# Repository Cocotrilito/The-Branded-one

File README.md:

<div align="center">

# The Branded One

*A tribute to Kentaro Miura's legacy.*

<br>

</div>

---

## Overview

A Berserk-themed NFC business card.
No battery.
No switches.
Powered entirely by your phone's NFC field.
Tap it and it opens my GitHub.

Built as a tribute to Guts' philosophy: **keep moving forward, no matter what.**

---

## The Tap

<p align="center">
  <i>No battery. No switches. Just the phone's field.</i>
</p>

---

## In Real Life

<p align="center">
  <i>The Branded One carried as it was meant to be.</i>
</p>

<br>

---

## The reason behind this project

> This project started with the Idea of showing a little bit of respect or give some honor for one of the most influencial characters in my adolescence, Gats or Guts or Gustavo in spanish, I wanted to do the business card, but It did not felt like me what can I say... I did not liked the Idea of a plain card, and is not useful Imo, so instead of a business card, why not a meaningfull memento, you see Guts really inspired me to keep going, probably thanks to what I read when I was younger I am who I am now, theres this quote of Guts that really hits me, it says...
>
> **I'm not going to die here.**
>
> to me it represents my hunger for not dying as a normal human being, everyday I try to do something to push me more, and its because I dont wanna be normal, and I started having sparks of this type of life, when Guts went out on a journey, leaving to become someone, thats when I thought,
>
> **Why am I not doing that...**
>
> thanks Guts, probably I will never see the ending of Berserk, but it did teach me to not give up, even when you dont think is worth it to try one more time, when you are worried about what will happen, you have to think the real reason you started, and in the process dont try to always be happy, just live because life is about living the present, not the past neither the future.
>
> **If Guts did not surrender, Why would you?**

---

## Schematic

---

## PCB

<table>
  <tr>
    <td width="50%"></td>
    <td width="50%"></td>
  </tr>
  <tr>
    <td align="center"><b>Front Copper</b></td>
    <td align="center"><b>Back Copper</b></td>
  </tr>
</table>

---

## Renders

<table>
  <tr>
    <td width="50%"></td>
    <td width="50%"></td>
  </tr>
  <tr>
    <td align="center"><b>Front</b></td>
    <td align="center"><b>Back</b></td>
  </tr>
</table>

---

## Bill of Materials

| Name | Purpose | Qty | Total Cost (USD) | Link |
| :--- | :--- | :---: | :---: | :--- |
| NT3H2111W0FHKH | NFC Controller | 1 | 0.62 | [LCSC](https://www.lcsc.com/product-detail/C710403.html) |
| Red LED 0603 | Status LED | 1 | 0.02 | [LCSC](https://www.lcsc.com/product-detail/C2286.html) |
| 1kΩ Resistor | LED Protection | 1 | 0.01 | [LCSC](https://www.lcsc.com/product-detail/C21190.html) |
| 100nF Capacitor | Decoupling Capacitor | 1 | 0.01 | [LCSC](https://www.lcsc.com/product-detail/C14663.html) |

---

## Special Thanks

To *三浦 建太郎*,
and to my family that allowed me to be here,
and also...

**STASIS <3333**
**Hack Club**

---

## You might also like

- [The Dichotomy Split](https://github.com/Cocotrilito/The-Dichotomy-Split)
- [Voyager Panel](https://github.com/Cocotrilito/Voyager-Panel)
- [Chimborazo Stratos-1](https://github.com/Cocotrilito/Chimborazo-Stratos-1)

---

## Final thanks

To me,
thanks for surviving every night,
even with the brand.
Thanks for fighting back,
and for not giving up on the Idea of changing our destiny.

> **"I'm not going to die here."**
>
> — *Guts*

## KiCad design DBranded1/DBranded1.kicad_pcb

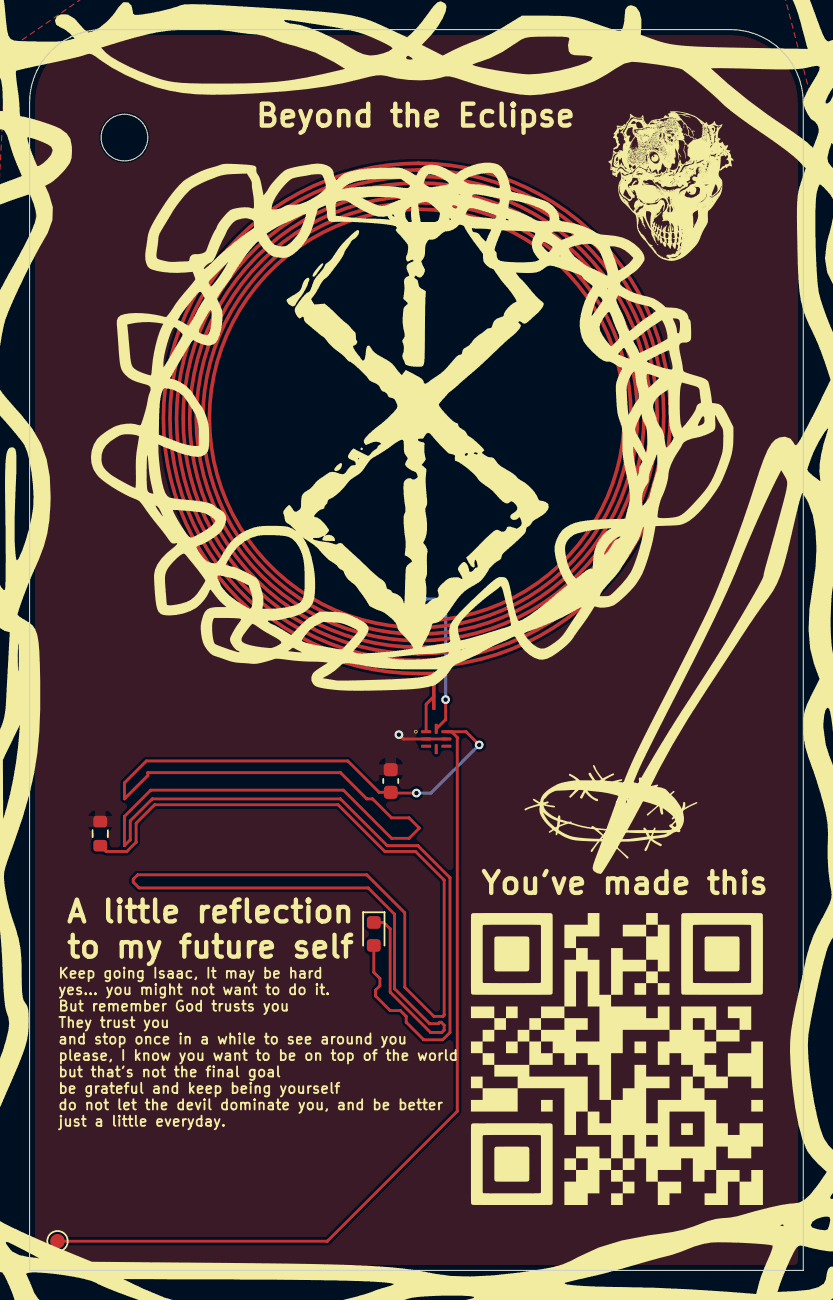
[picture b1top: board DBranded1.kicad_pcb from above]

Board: 2 copper layers, 53.0 x 85.0 mm, 5 parts (0 on the bottom side), 3 nets.

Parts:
C1: 100nF; C_0603_1608Metric
D1: LED; LED_0603_1608Metric
R1: 220; R_0603_1608Metric
TP1: TestPoint; TestPoint_Pad_D1.0mm
U1: NT3H2111W0FHKH; QFN8P50_160X160X50L40X20N

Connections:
GND: C1.1, R1.1, U1.2 (VSS), U1.6 (VCC)
unnamed: C1.2, D1.2 (A), TP1.1 (1_1), U1.7 (VOUT)
unnamed: D1.1 (K), R1.2

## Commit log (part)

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2026-05-02 Schematic and PCB
2026-05-02 bom and production files
2026-05-02 Added final render and pictures
2026-05-02 Revise README for project clarity and presentation
    Updated README.md to enhance project description and layout.
